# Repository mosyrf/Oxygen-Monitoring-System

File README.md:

# Oxygen-Monitoring-System
This was my second year project as an electrical engineering student, and it was quite difficult because it used an STM32 controller, which I was not familiar with. The project was also considered a failure because it did not produce any final product, only electrical designs and simulations.

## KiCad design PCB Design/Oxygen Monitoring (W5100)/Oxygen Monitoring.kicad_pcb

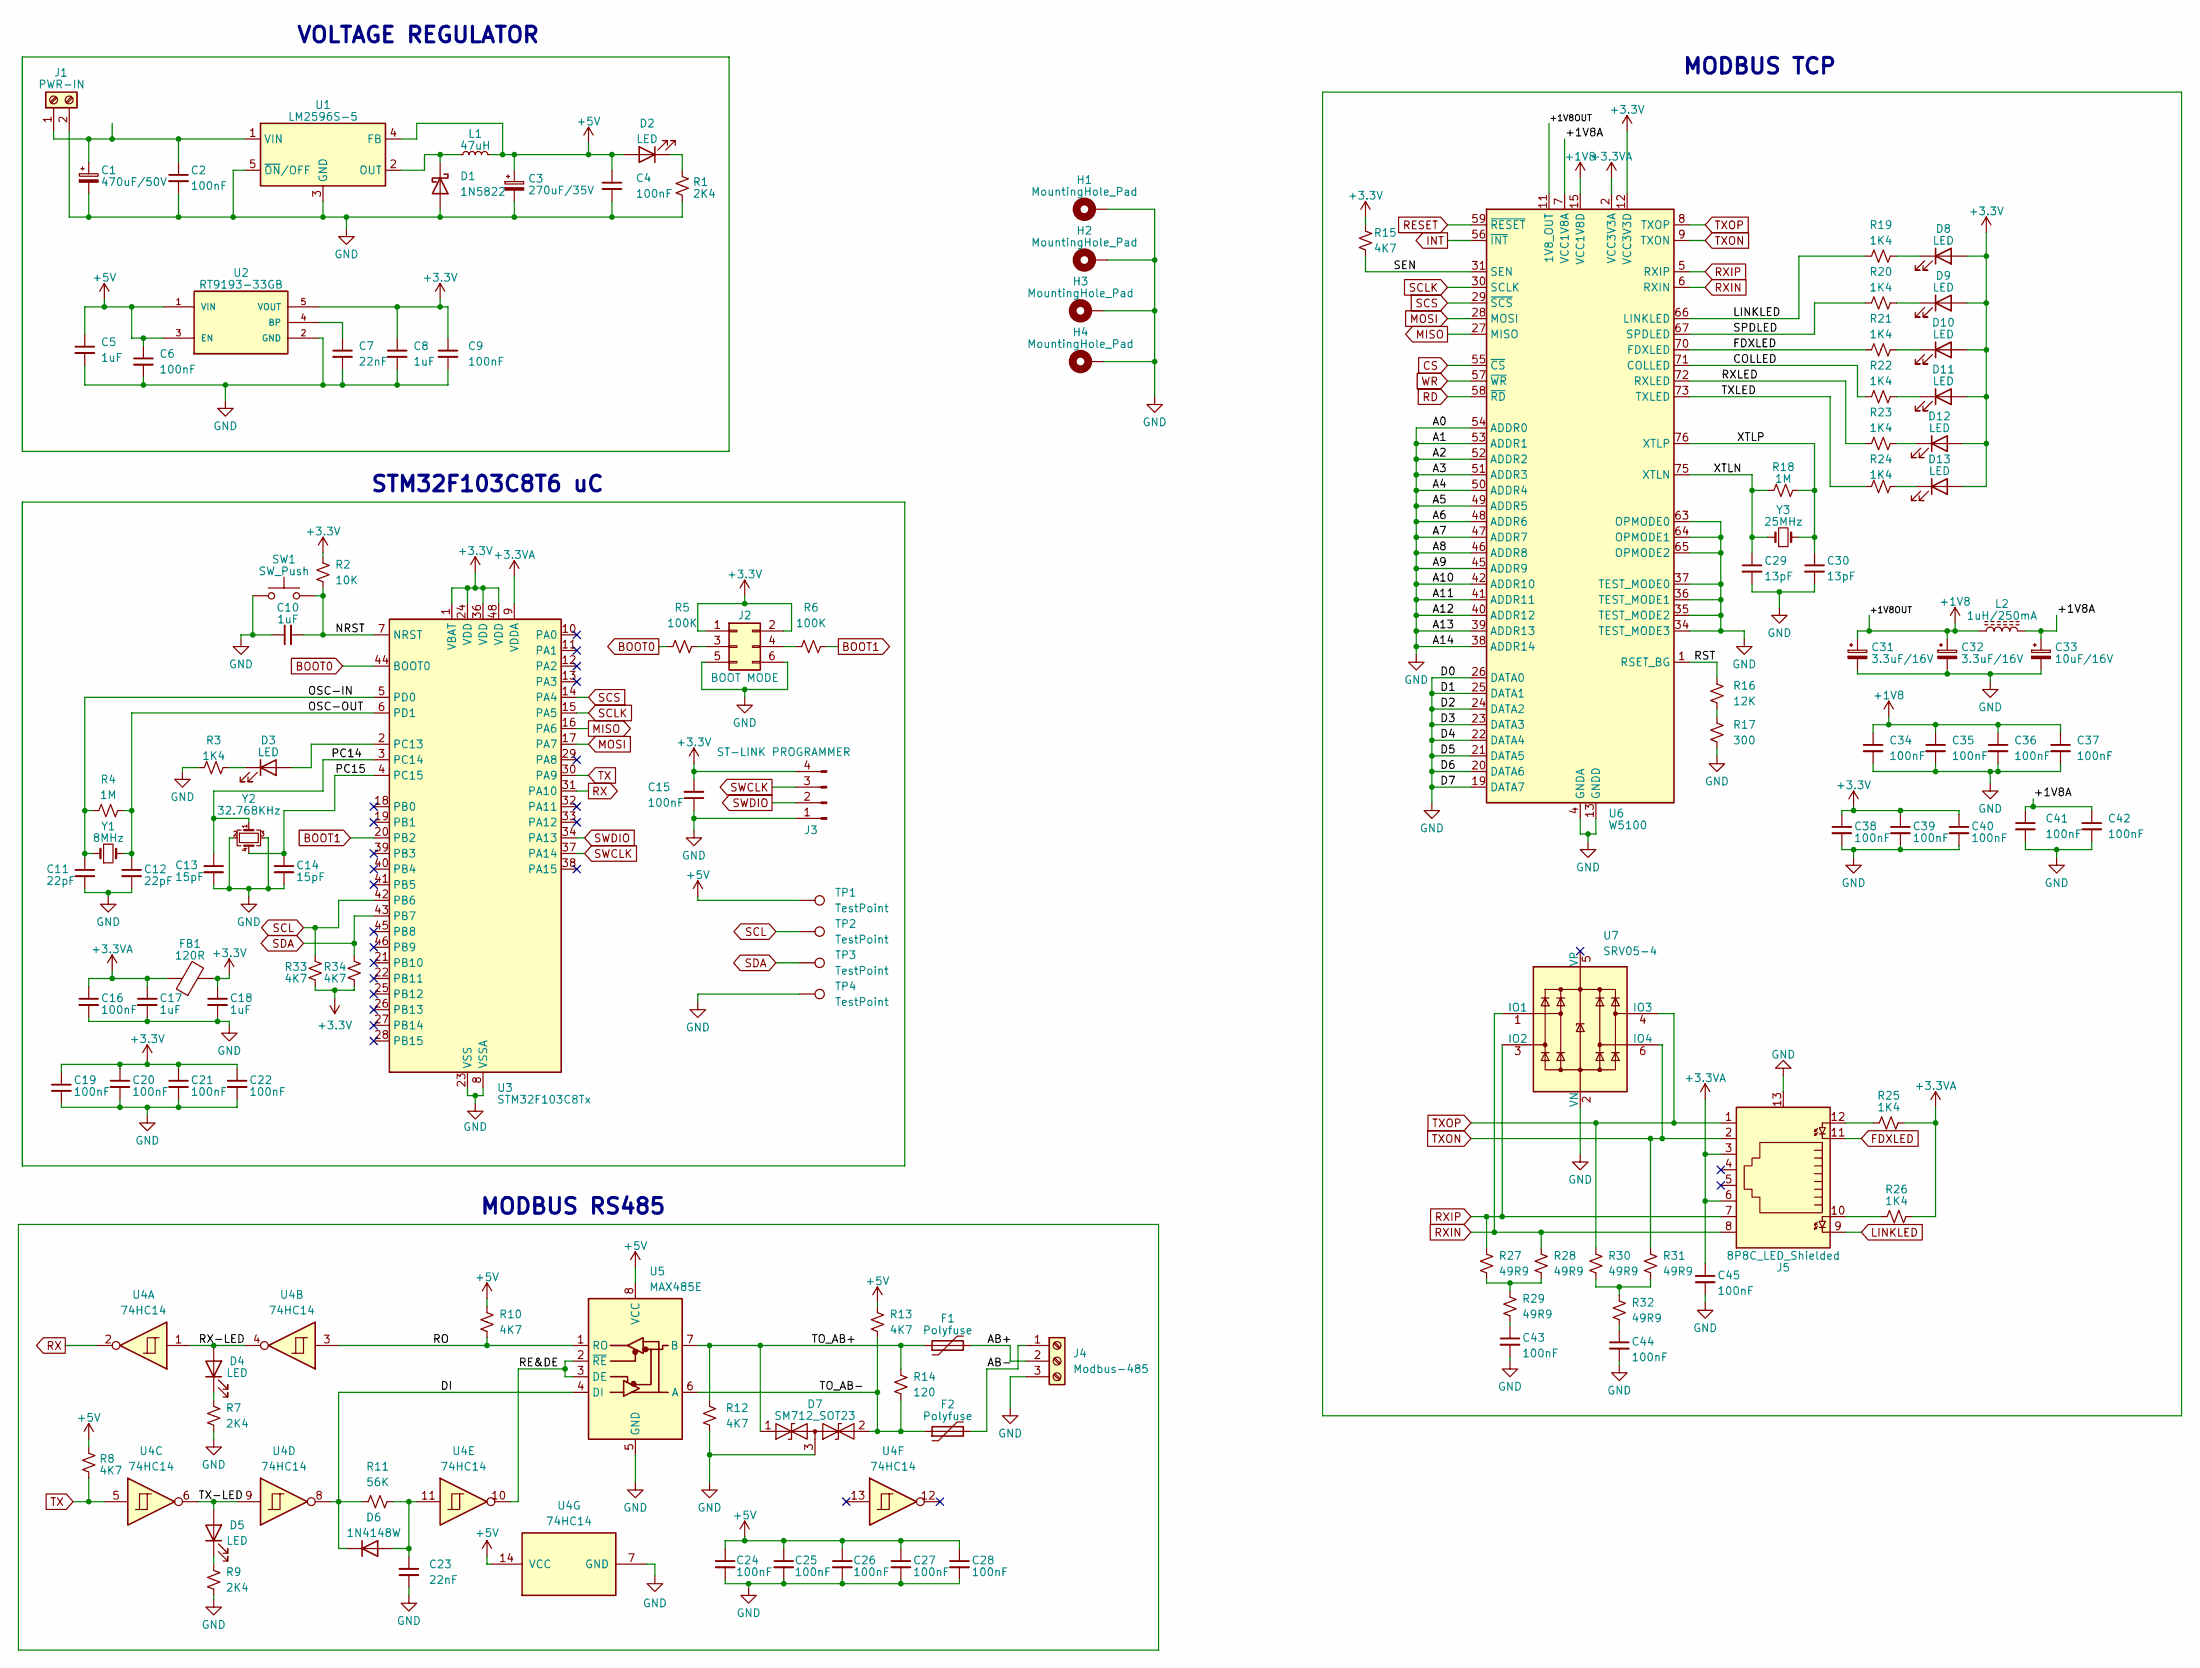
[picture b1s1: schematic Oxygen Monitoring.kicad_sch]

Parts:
C1: 470uF/50V; CP_Radial_D10.0mm_P7.50mm
C2, C4, C6, C9, C15, C16, C19, C20, C21, C22, C24, C25, C26, C27, C28, C34, C35, C36, C37, C38, C39, C40, C41, C42, C43, C44, C45: 100nF; C_0805_2012Metric
C3: 270uF/35V; CP_Radial_D8.0mm_P5.00mm
C5, C8, C10, C17, C18: 1uF; C_0805_2012Metric
C7, C23: 22nF; C_0805_2012Metric
C11, C12: 22pF; C_0805_2012Metric
C13, C14: 15pF; C_0805_2012Metric
C29, C30: 13pF; C_0805_2012Metric
C31, C32: 3.3uF/16V; CP_Radial_D4.0mm_P2.00mm
C33: 10uF/16V; CP_Radial_D5.0mm_P2.00mm
D1: 1N5822; D_DO-201AD_P12.70mm_Horizontal
D2, D3, D4, D5, D8, D9, D10, D11, D12, D13: LED; LED_0805_2012Metric
D6: 1N4148W; D_SOD-123
D7: SM712_SOT23; SOT-23
F1, F2: Polyfuse; Fuse_Littelfuse_395Series
FB1: 120R; L_0805_2012Metric
H1, H2, H3, H4: MountingHole_Pad; MountingHole_3mm_Pad_Via
J1: PWR-IN; TerminalBlock_Phoenix_PT-1,5-2-5.0-H_1x02_P5.00mm_Horizontal
J2: BOOT MODE; PinHeader_2x03_P2.54mm_Vertical
J3: ST-LINK PROGRAMMER; PinHeader_1x04_P2.54mm_Vertical
J4: Modbus-485; TerminalBlock_Phoenix_PT-1,5-3-5.0-H_1x03_P5.00mm_Horizontal
J5: 8P8C_LED_Shielded; RJ45_Cetus_J1B1211CCD_Horizontal
L1: 47uH; L_12x12mm_H4.5mm
L2: 1uH/250mA; L_0805_2012Metric
R1, R7, R9: 2K4; R_0805_2012Metric
R2: 10K; R_0805_2012Metric
R3, R19, R20, R21, R22, R23, R24, R25, R26: 1K4; R_0805_2012Metric
R4, R18: 1M; R_0805_2012Metric
R5, R6: 100K; R_0805_2012Metric
R8, R10, R12, R13, R15, R33, R34: 4K7; R_0805_2012Metric
R11: 56K; R_0805_2012Metric
R14: 120; R_0805_2012Metric
R16: 12K; R_0805_2012Metric
R17: 300; R_0805_2012Metric
R27, R28, R29, R30, R31, R32: 49R9; R_0805_2012Metric
SW1: SW_Push; SW_SPST_CK_RS282G05A3
TP1, TP2, TP3, TP4: TestPoint; SolderWirePad_1x01_SMD_1x2mm
U1: LM2596S-5; TO-263-5_TabPin3
U2: RT9193-33GB; SOT94P279X129-5N
U3: STM32F103C8Tx; LQFP-48_7x7mm_P0.5mm
U4: 74HC14; DIP-14_W7.62mm_SMDSocket_SmallPads
U5: MAX485E; DIP-8_W7.62mm_SMDSocket_SmallPads
U6: W5100; LQFP-80_10x10mm_P0.4mm
U7: SRV05-4; SOT-23-6
Y1: 8MHz; Crystal_HC49-U_Vertical
Y2: 32.768KHz; Crystal_SMD_SeikoEpson_MC156-4Pin_7.1x2.5mm_HandSoldering
Y3: 25MHz; Crystal_HC49-U_Vertical

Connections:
+1V8: C31.1, C32.1, C34.1, C35.1, C36.1, C37.1, L2.1, U6.11 (1V8_OUT), U6.15 (VCC1V8D), U6.16 (VCC1V8D), U6.33 (VCC1V8D), U6.69 (VCC1V8D)
+3.3V: C8.1, C9.1, C15.2, C18.1, C19.1, C20.1, C21.1, C22.1, C38.1, C39.1, C40.1, D8.2 (A), D9.2 (A), D10.2 (A), D11.2 (A), D12.2 (A), D13.2 (A), FB1.2, J2.1, J2.2, J3.4, R2.1, R15.2, R33.2, R34.2, U2.5 (VOUT), U3.1 (VBAT), U3.24 (VDD), U3.36 (VDD), U3.48 (VDD), U6.12 (VCC3V3D), U6.18 (VCC3V3D), U6.44 (VCC3V3D)
+3.3VA: C16.1, C17.1, C45.1, FB1.1, J5.3, J5.6, R25.2, R26.2, U3.9 (VDDA), U6.2 (VCC3V3A)
+5V: C3.1, C4.1, C5.1, C6.1, C24.1, C25.1, C26.1, C27.1, C28.1, D2.2 (A), L1.2, R8.2, R10.2, R13.2, TP1.1, U1.4 (FB), U2.1 (VIN), U2.3 (EN), U4.14 (VCC), U5.8 (VCC)
/+1V8A: C33.1, C41.1, C42.1, L2.2, U6.7 (VCC1V8A), U6.74 (VCC1V8A)
/AB+: F1.2, J4.2
/AB-: F2.2, J4.1
/COLLED: R22.1, U6.71 (COLLED)
/DI: D6.1 (K), R11.2, U4.8, U5.4 (DI)
/NRST: C10.2, R2.2, SW1.2, U3.7 (NRST)
/OSC-IN: C11.1, R4.1, U3.5 (PD0), Y1.1
/OSC-OUT: C12.1, R4.2, U3.6 (PD1), Y1.2
/PC14: C13.1, U3.3 (PC14), Y2.1
/PC15: C14.1, U3.4 (PC15), Y2.4
/RE&DE: U4.10, U5.2 (~RE), U5.3 (DE)
/RO: R10.1, U4.3, U5.1 (RO)
/RST: R16.1, U6.1 (RSET_BG)
/RX-LED: D4.2 (A), U4.1, U4.4
/RXLED: R23.1, U6.72 (RXLED)
/SEN: R15.1, U6.31 (SEN)
/SPDLED: R20.1, U6.67 (SPDLED)
/TO_AB+: D7.1 (A1), F1.1, R12.2, R14.2, U5.7 (B)
/TO_AB-: D7.2 (A2), F2.1, R13.1, R14.1, U5.6 (A)
/TX-LED: D5.2 (A), U4.6, U4.9
/TXLED: R24.1, U6.73 (TXLED)
/XTLN: C29.1, R18.1, U6.75 (XTLN), Y3.1
/XTLP: C30.1, R18.2, U6.76 (XTLP), Y3.2
BOOT0: R5.1, U3.44 (BOOT0)
BOOT1: R6.2, U3.20 (PB2)
CS: U6.55 (~CS)
FDXLED: J5.11, R21.1, U6.70 (FDXLED)
GND: C1.2, C2.2, C3.2, C4.2, C5.2, C6.2, C7.2, C8.2, C9.2, C10.1, C11.2, C12.2, C13.2, C14.2, C15.1, C16.2, C17.2, C18.2, C19.2, C20.2, C21.2, C22.2, C23.2, C24.2, C25.2, C26.2, C27.2, C28.2, C29.2, C30.2, C31.2, C32.2, C33.2, C34.2, C35.2, C36.2, C37.2, C38.2, C39.2, C40.2, C41.2, C42.2, C43.2, C44.2, C45.2, D1.2 (A), D7.3 (common), H1.1, H2.1, H3.1, H4.1, J1.2, J2.5, J2.6, J3.1, J4.3, J5.13, R1.2, R3.1, R7.1, R9.1, R12.1, R17.1, SW1.1, TP4.1, U1.3 (GND), U1.5 (~ON/OFF), U2.2 (GND), U3.8 (VSSA), U3.23 (VSS), U3.35 (VSS), U3.47 (VSS), U4.7 (GND), U5.5 (GND), U6.4 (GNDA), U6.10 (GNDA), U6.13 (GNDD), U6.14 (GNDD), U6.17 (GNDD), U6.19 (DATA7), U6.20 (DATA6), U6.21 (DATA5), U6.22 (DATA4), U6.23 (DATA3), U6.24 (DATA2), U6.25 (DATA1), U6.26 (DATA0), U6.32 (GNDD), U6.34 (TEST_MODE3), U6.35 (TEST_MODE2), U6.36 (TEST_MODE1), U6.37 (TEST_MODE0), U6.38 (ADDR14), U6.39 (ADDR13), U6.40 (ADDR12), U6.41 (ADDR11), U6.42 (ADDR10), U6.43 (GNDD), U6.45 (ADDR9), U6.46 (ADDR8), U6.47 (ADDR7), U6.48 (ADDR6), U6.49 (ADDR5), U6.50 (ADDR4), U6.51 (ADDR3), U6.52 (ADDR2), U6.53 (ADDR1), U6.54 (ADDR0), U6.63 (OPMODE0), U6.64 (OPMODE1), U6.65 (OPMODE2), U6.68 (GNDD), U6.77 (GNDA), U7.2 (VN), Y2.2, Y2.3
INT: U6.56 (~INT)
LINKLED: J5.9, R19.1, U6.66 (LINKLED)
MISO: U3.16 (PA6), U6.27 (MISO)
MOSI: U3.17 (PA7), U6.28 (MOSI)
unnamed: C43.1, R29.2
unnamed: C44.1, R32.2
unnamed: D1.1 (K), L1.1, U1.2 (OUT)
unnamed: D2.1 (K), R1.1
unnamed: D3.2 (A), U3.2 (PC13)
unnamed: D3.1 (K), R3.2
unnamed: D4.1 (K), R7.2
unnamed: D5.1 (K), R9.2
unnamed: C23.1, D6.2 (A), R11.1, U4.11
unnamed: D8.1 (K), R19.2
unnamed: D9.1 (K), R20.2
unnamed: D10.1 (K), R21.2
unnamed: D11.1 (K), R22.2
unnamed: D12.1 (K), R23.2
unnamed: D13.1 (K), R24.2
unnamed: C1.1, C2.1, J1.1, U1.1 (VIN)
unnamed: J2.3, R5.2
unnamed: J2.4, R6.1
unnamed: J5.10, R26.1
unnamed: J5.12, R25.1
unnamed: R16.2, R17.2
unnamed: R27.2, R28.2, R29.1
unnamed: R30.2, R31.2, R32.1
unnamed: C7.1, U2.4 (BP)
RD: U6.58 (~RD)
RESET: U6.59 (~RESET)
RX: U3.31 (PA10), U4.2
RXIN: J5.8, R28.1, U6.6 (RXIN), U7.1 (IO1)
RXIP: J5.7, R27.1, U6.5 (RXIP), U7.3 (IO2)
SCL: R33.1, TP2.1, U3.42 (PB6)
SCLK: U3.15 (PA5), U6.30 (SCLK)
SCS: U3.14 (PA4), U6.29 (~SCS)
SDA: R34.1, TP3.1, U3.43 (PB7)
SWCLK: J3.3, U3.37 (PA14)
SWDIO: J3.2, U3.34 (PA13)
TX: R8.1, U3.30 (PA9), U4.5
TXON: J5.2, R31.1, U6.9 (TXON), U7.6 (IO4)
TXOP: J5.1, R30.1, U6.8 (TXOP), U7.4 (IO3)
WR: U6.57 (~WR)

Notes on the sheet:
VOLTAGE REGULATOR
MODBUS TCP
STM32F103C8T6 uC
MODBUS RS485

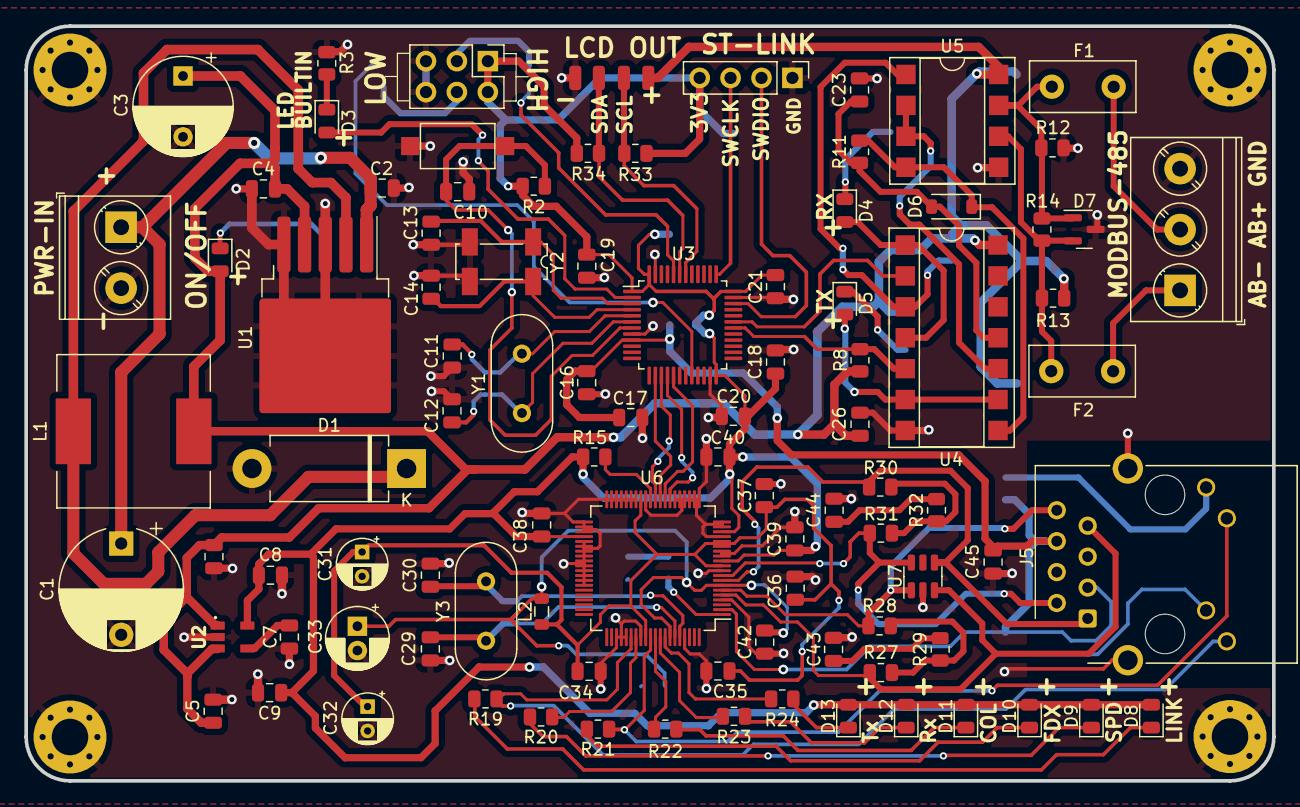
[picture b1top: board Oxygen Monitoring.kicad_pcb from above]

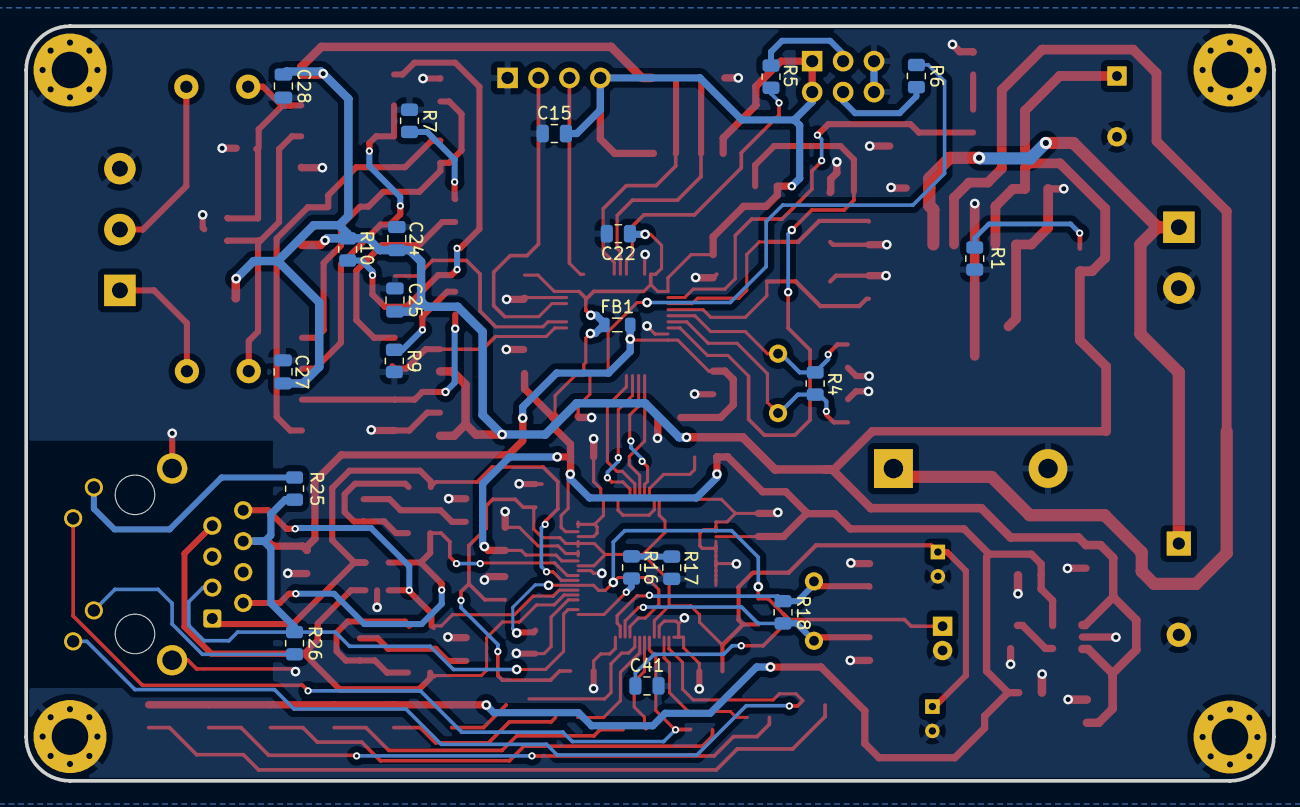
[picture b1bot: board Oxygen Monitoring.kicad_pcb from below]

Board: 2 copper layers, 102.5 x 62.0 mm, 121 parts (20 on the bottom side), 70 nets.

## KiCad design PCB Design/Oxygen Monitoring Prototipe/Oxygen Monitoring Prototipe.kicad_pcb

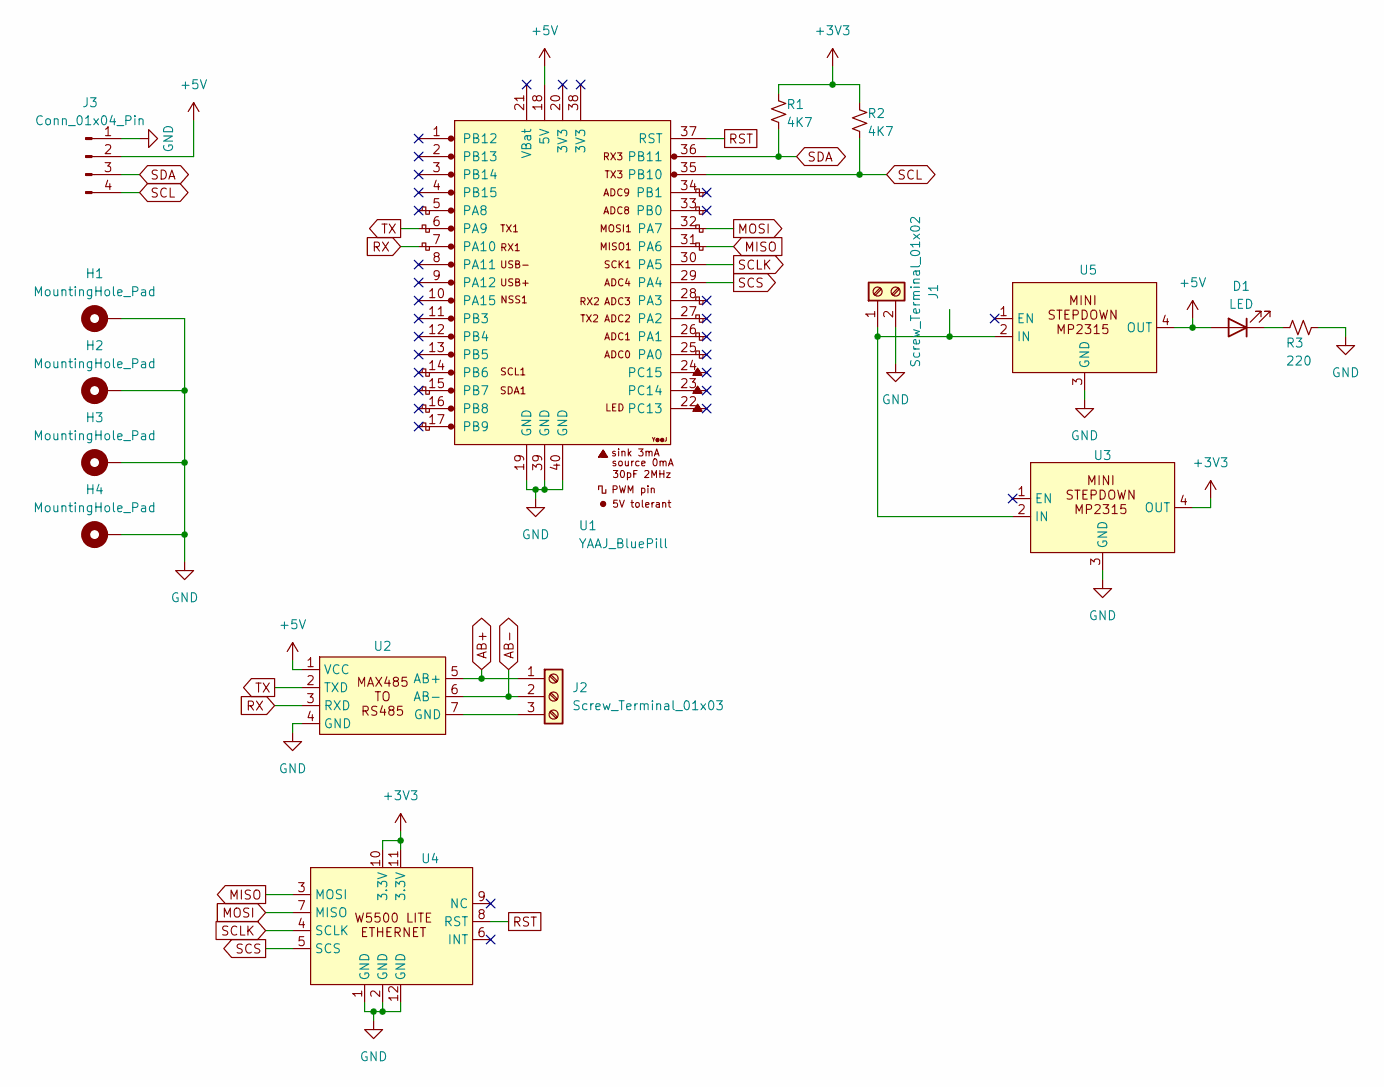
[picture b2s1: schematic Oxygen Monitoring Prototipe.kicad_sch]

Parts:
D1: LED; LED_D5.0mm
H1, H2, H3, H4: MountingHole_Pad; MountingHole_3.2mm_M3_Pad_Via
J1: Screw_Terminal_01x02; TerminalBlock_Phoenix_MKDS-3-2-5.08_1x02_P5.08mm_Horizontal
J2: Screw_Terminal_01x03; TerminalBlock_Phoenix_MKDS-3-3-5.08_1x03_P5.08mm_Horizontal
J3: Conn_01x04_Pin; PinHeader_1x04_P2.54mm_Vertical
R1, R2: 4K7; R_Axial_DIN0204_L3.6mm_D1.6mm_P5.08mm_Horizontal
R3: 220; R_Axial_DIN0204_L3.6mm_D1.6mm_P5.08mm_Horizontal
U1: YAAJ_BluePill; YAAJ_BluePill_1
U2: MAX485_AutoSwitching&Protection
U3, U5: MP2315_Module
U4: W5500_Lite

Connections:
+3V3: R1.1, R2.1, U3.4 (OUT), U4.10 (3.3V), U4.11 (3.3V)
+5V: D1.2 (A), J3.2, U1.18 (5V), U2.1 (VCC), U5.4 (OUT)
AB+: J2.1, U2.5 (AB+)
AB-: J2.2, U2.6 (AB-)
GND: H1.1, H2.1, H3.1, H4.1, J1.2, J3.1, R3.1, U1.19 (GND), U1.39 (GND), U1.40 (GND), U2.4 (GND), U3.3 (GND), U4.1 (GND), U4.2 (GND), U4.12 (GND), U5.3 (GND)
MISO: U1.31 (PA6), U4.3 (MOSI)
MOSI: U1.32 (PA7), U4.7 (MISO)
unnamed: D1.1 (K), R3.2
unnamed: J1.1, U3.2 (IN), U5.2 (IN)
unnamed: J2.3, U2.7 (GND)
RST: U1.37 (RST), U4.8 (RST)
RX: U1.7 (PA10), U2.3 (RXD)
SCL: J3.4, R2.2, U1.35 (PB10)
SCLK: U1.30 (PA5), U4.4 (SCLK)
SCS: U1.29 (PA4), U4.5 (SCS)
SDA: J3.3, R1.2, U1.36 (PB11)
TX: U1.6 (PA9), U2.2 (TXD)

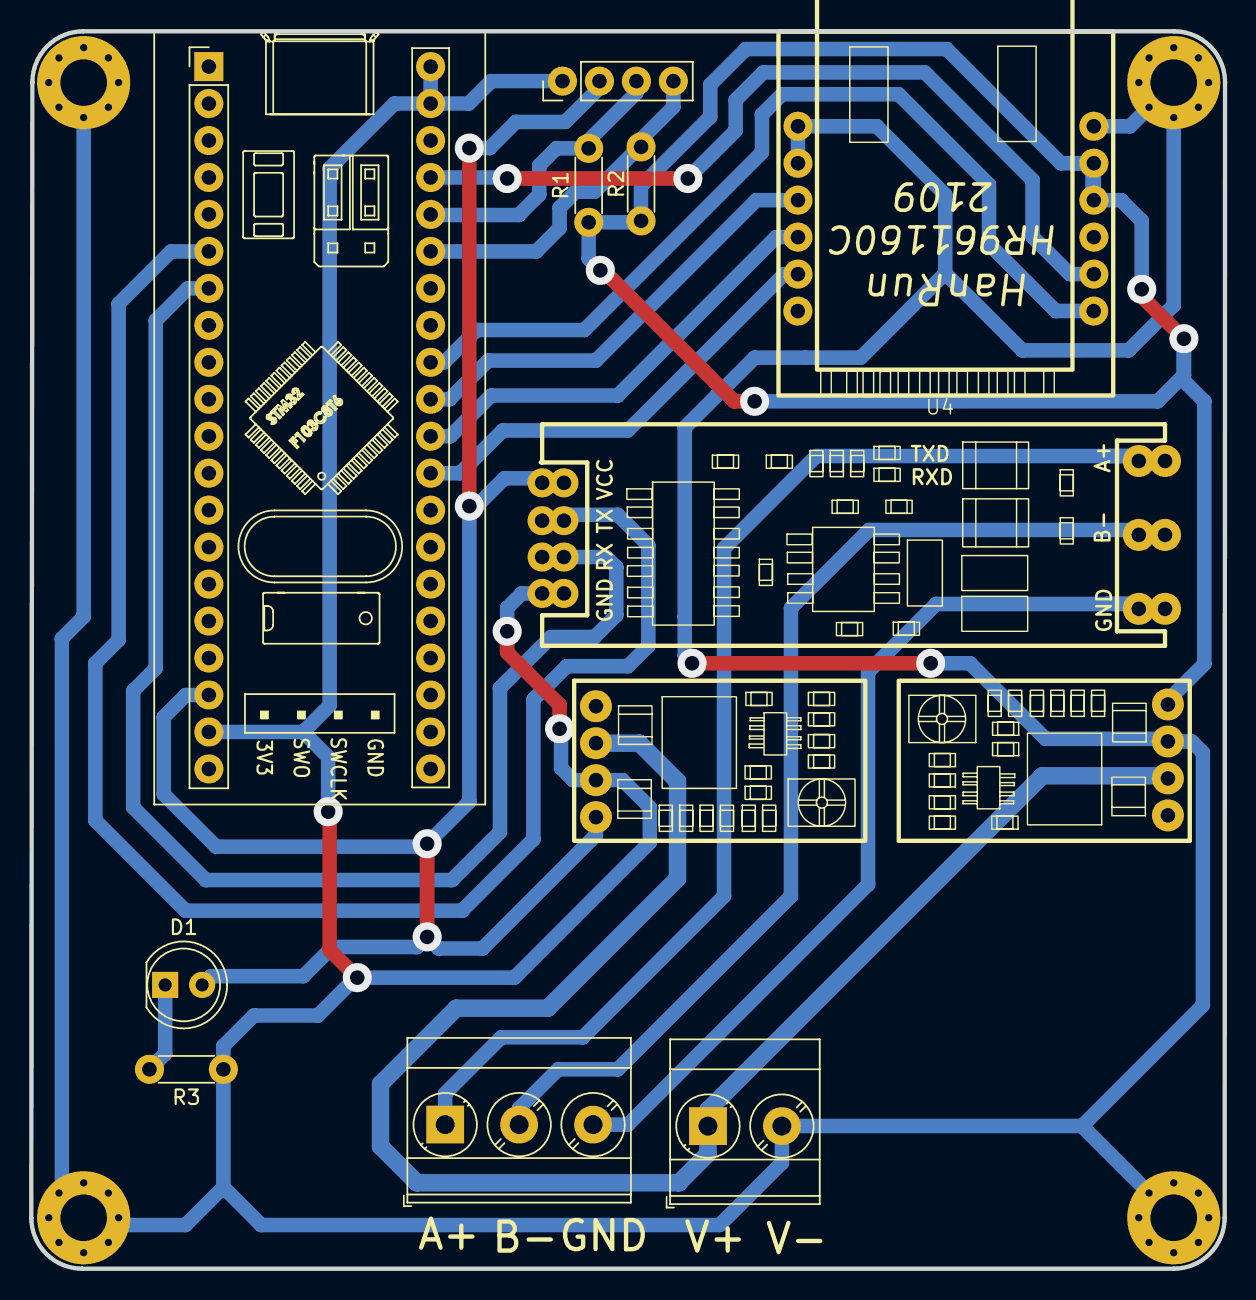
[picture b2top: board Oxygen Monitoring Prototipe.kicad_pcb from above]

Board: 2 copper layers, 82.0 x 85.0 mm, 16 parts (0 on the bottom side), 17 nets.

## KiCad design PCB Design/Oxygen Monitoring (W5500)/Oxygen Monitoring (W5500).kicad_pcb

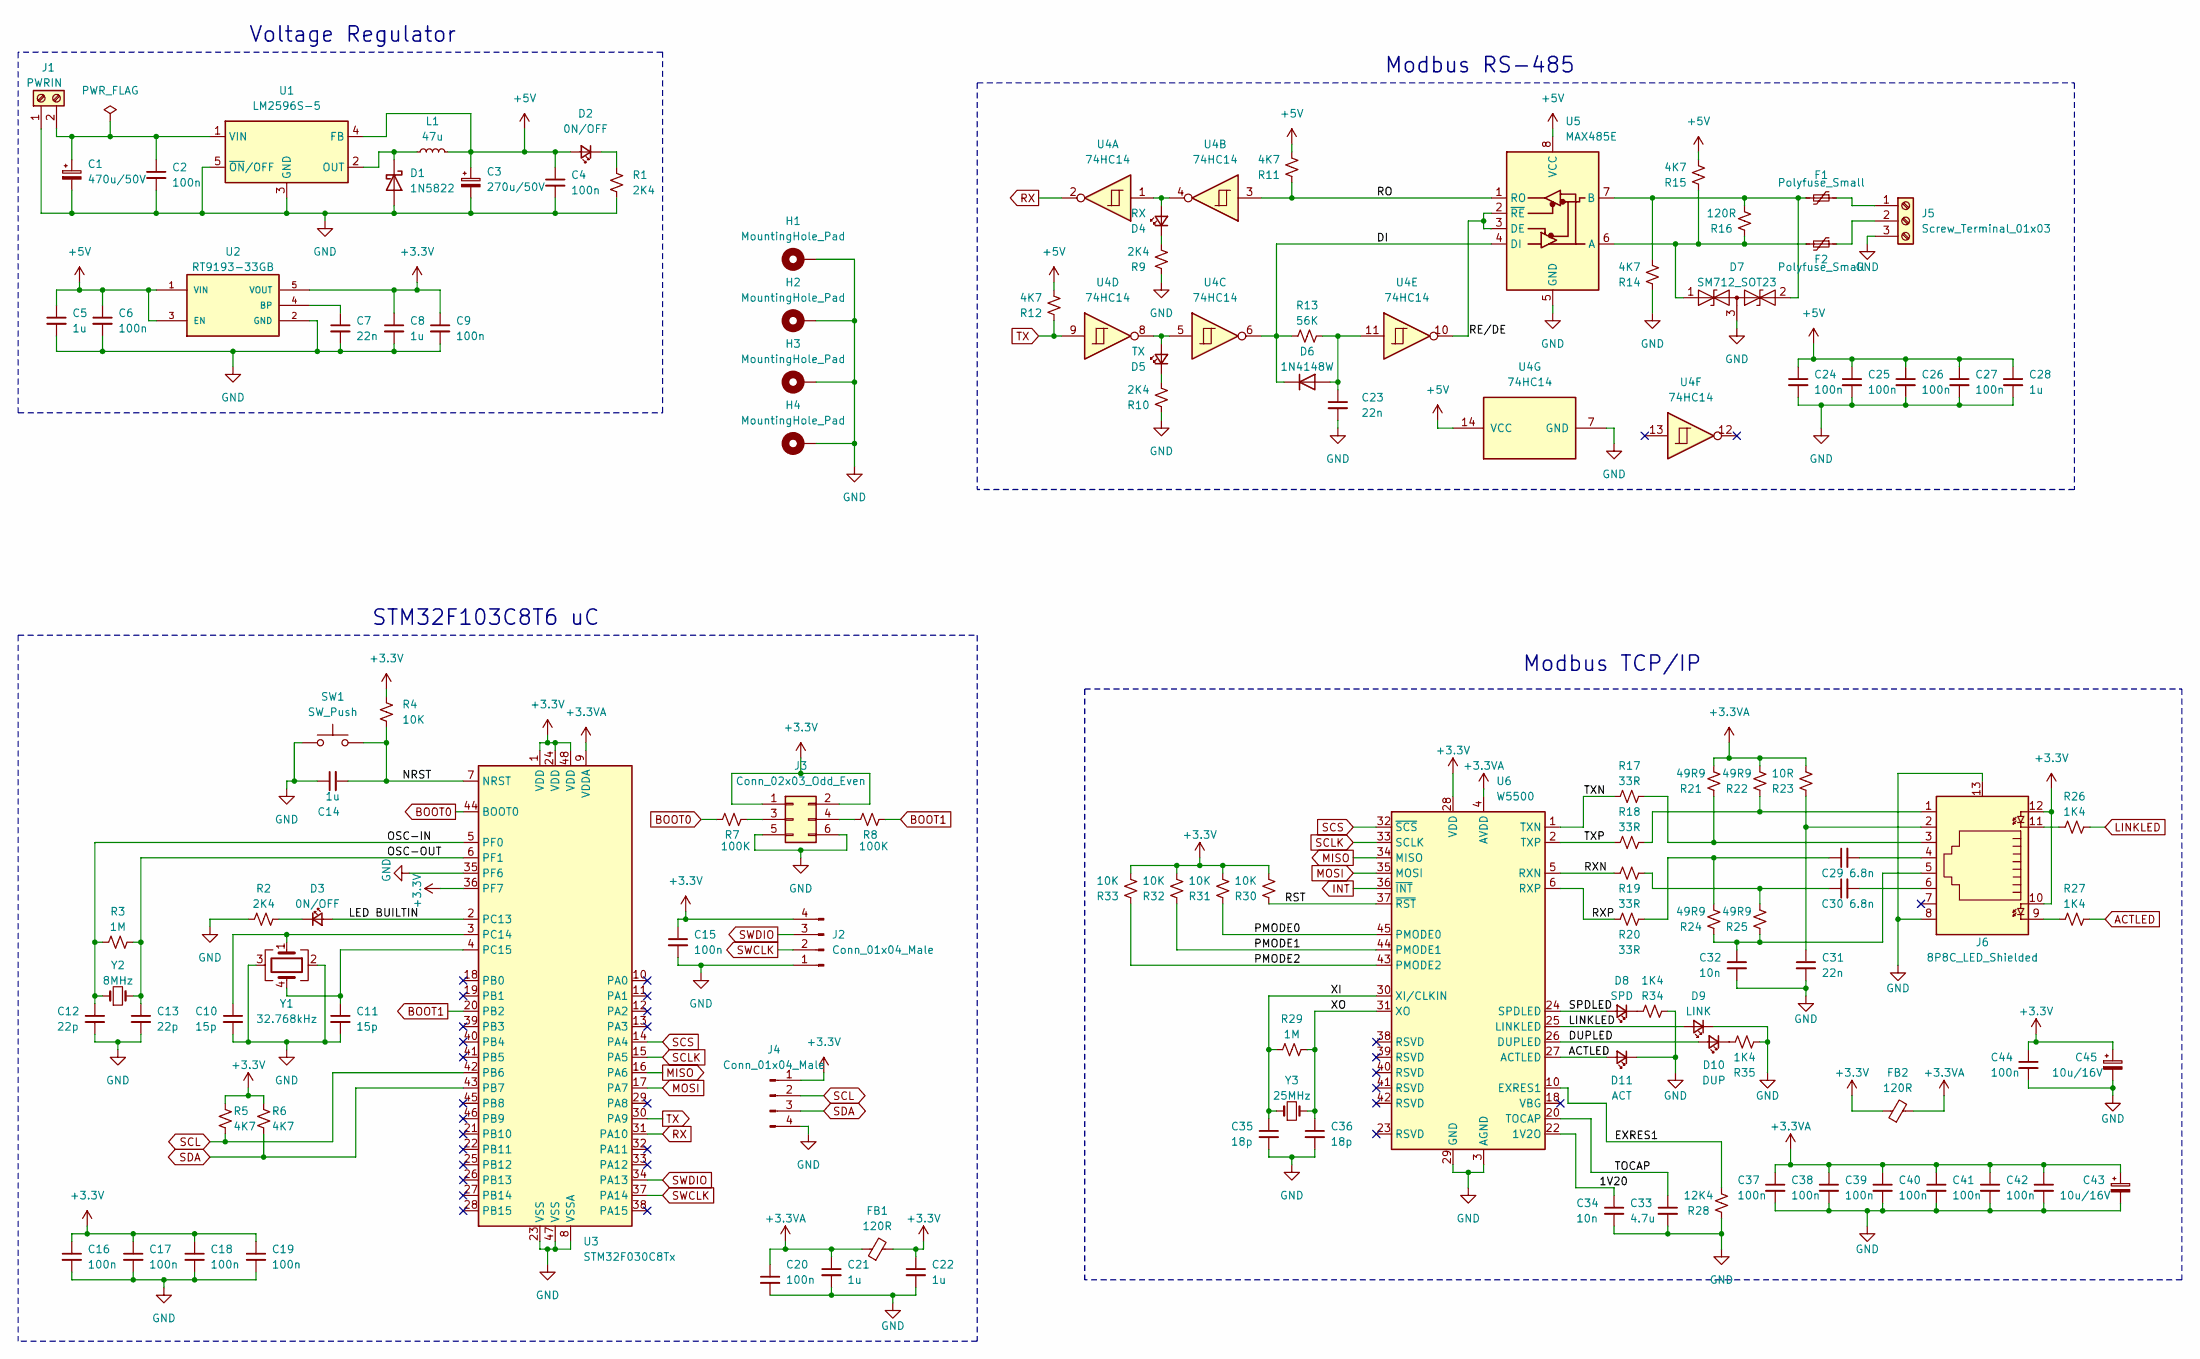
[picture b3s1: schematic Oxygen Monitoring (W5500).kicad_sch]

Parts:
C1: 470u/50V; CP_Radial_D6.3mm_P2.50mm
C2, C4, C6, C9, C15, C16, C17, C18, C19, C20, C24, C25, C26, C27, C37, C38, C39, C40, C41, C42, C44: 100n; C_0805_2012Metric_Pad1.18x1.45mm_HandSolder
C3: 270u/50V; CP_Radial_D5.0mm_P2.50mm
C5, C8, C14, C21, C22, C28: 1u; C_0805_2012Metric_Pad1.18x1.45mm_HandSolder
C7, C23, C31: 22n; C_0805_2012Metric_Pad1.18x1.45mm_HandSolder
C10, C11: 15p; C_0805_2012Metric_Pad1.18x1.45mm_HandSolder
C12, C13: 22p; C_0805_2012Metric_Pad1.18x1.45mm_HandSolder
C29, C30: 6.8n; C_0805_2012Metric_Pad1.18x1.45mm_HandSolder
C32, C34: 10n; C_0805_2012Metric_Pad1.18x1.45mm_HandSolder
C33: 4.7u; C_0805_2012Metric_Pad1.18x1.45mm_HandSolder
C35, C36: 18p; C_0805_2012Metric_Pad1.18x1.45mm_HandSolder
C43, C45: 10u/16V; CP_Radial_D4.0mm_P1.50mm
D1: 1N5822; D_DO-201AD_P15.24mm_Horizontal
D2, D3: 0N/OFF; LED_0805_2012Metric_Pad1.15x1.40mm_HandSolder
D4: RX; LED_0805_2012Metric_Pad1.15x1.40mm_HandSolder
D5: TX; LED_0805_2012Metric_Pad1.15x1.40mm_HandSolder
D6: 1N4148W; D_SOD-123
D7: SM712_SOT23; SOT-23
D8: SPD; LED_0805_2012Metric_Pad1.15x1.40mm_HandSolder
D9: LINK; LED_0805_2012Metric_Pad1.15x1.40mm_HandSolder
D10: DUP; LED_0805_2012Metric_Pad1.15x1.40mm_HandSolder
D11: ACT; LED_0805_2012Metric_Pad1.15x1.40mm_HandSolder
F1, F2: Polyfuse_Small; Fuse_1210_3225Metric_Pad1.42x2.65mm_HandSolder
FB1, FB2: 120R; L_0805_2012Metric_Pad1.15x1.40mm_HandSolder
H1, H2, H3, H4: MountingHole_Pad; MountingHole_3.2mm_M3_Pad_Via
J1: PWRIN; TerminalBlock_Phoenix_MKDS-1,5-2-5.08_1x02_P5.08mm_Horizont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
J2: Conn_01x04_Male; PinHeader_1x04_P2.54mm_Vertical
J3: Conn_02x03_Odd_Even; PinHeader_2x03_P2.54mm_Vertical
J4: Conn_01x04_Male; Molex_KK-254_AE-6410-04A_1x04_P2.54mm_Vertical
J5: Screw_Terminal_01x03; TerminalBlock_Phoenix_MKDS-1,5-3-5.08_1x03_P5.08mm_Horizont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
J6: 8P8C_LED_Shielded; RJ45_Cetus_J1B1211CCD_Horizontal
L1: 47u; L_12x12mm_H6mm
R1, R2, R9, R10: 2K4; R_0805_2012Metric_Pad1.20x1.40mm_HandSolder
R3, R29: 1M; R_0805_2012Metric_Pad1.20x1.40mm_HandSolder
R4, R30, R31, R32, R33: 10K; R_0805_2012Metric_Pad1.20x1.40mm_HandSolder
R5, R6, R11, R12, R14, R15: 4K7; R_0805_2012Metric_Pad1.20x1.40mm_HandSolder
R7, R8: 100K; R_0805_2012Metric_Pad1.20x1.40mm_HandSolder
R13: 56K; R_0805_2012Metric_Pad1.20x1.40mm_HandSolder
R16: 120R; R_0805_2012Metric_Pad1.20x1.40mm_HandSolder
R17, R18, R19, R20: 33R; R_0805_2012Metric_Pad1.20x1.40mm_HandSolder
R21, R22, R24, R25: 49R9; R_0805_2012Metric_Pad1.20x1.40mm_HandSolder
R23: 10R; R_0805_2012Metric_Pad1.20x1.40mm_HandSolder
R26, R27, R34, R35: 1K4; R_0805_2012Metric_Pad1.20x1.40mm_HandSolder
R28: 12K4; R_0805_2012Metric_Pad1.20x1.40mm_HandSolder
SW1: SW_Push; SW_SPST_TL3342
U1: LM2596S-5; TO-263-5_TabPin3
U2: RT9193-33GB; SOT-23-5_HandSoldering
U3: STM32F030C8Tx; LQFP-48_7x7mm_P0.5mm
U4: 74HC14; DIP-14_W7.62mm_SMDSocket_SmallPads
U5: MAX485E; DIP-8_W7.62mm_SMDSocket_SmallPads
U6: W5500; LQFP-48_7x7mm_P0.5mm
Y1: 32.768kHz; Crystal_SMD_SeikoEpson_MC156-4Pin_7.1x2.5mm_HandSoldering
Y2: 8MHz; Crystal_HC49-4H_Vertical
Y3: 25MHz; Crystal_HC49-4H_Vertical

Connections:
+3.3V: C8.1, C9.1, C15.1, C16.1, C17.1, C18.1, C19.1, C22.1, C44.1, C45.1, FB1.2, FB2.1, J2.4, J3.1, J3.2, J4.1, J6.10, J6.12, R4.1, R5.1, R6.1, R30.2, R31.2, R32.2, R33.2, U2.5 (VOUT), U3.1 (VDD), U3.24 (VDD), U3.36 (PF7), U3.48 (VDD), U6.28 (VDD)
+3.3VA: C20.1, C21.1, C37.1, C38.1, C39.1, C40.1, C41.1, C42.1, C43.1, FB1.1, FB2.2, R21.2, R22.2, R23.2, U3.9 (VDDA), U6.4 (AVDD), U6.8 (AVDD), U6.11 (AVDD), U6.15 (AVDD), U6.17 (AVDD), U6.21 (AVDD)
+5V: C3.1, C4.1, C5.1, C6.1, C24.1, C25.1, C26.1, C27.1, C28.1, D2.2 (A), L1.2, R11.2, R12.2, R15.2, U1.4 (FB), U2.1 (VIN), U2.3 (EN), U4.14 (VCC), U5.8 (VCC)
/1V20: C34.1, U6.22 (1V2O)
/DI: D6.1 (K), R13.1, U4.6, U5.4 (DI)
/DUPLED: D10.2 (A), U6.26 (DUPLED)
/EXRES1: R28.2, U6.10 (EXRES1)
/LED BUILTIN: D3.2 (A), U3.2 (PC13)
/NRST: C14.2, R4.2, SW1.2, U3.7 (NRST)
/OSC-IN: C12.1, R3.1, U3.5 (PF0), Y2.1
/OSC-OUT: C13.1, R3.2, U3.6 (PF1), Y2.2
/PMODE0: R31.1, U6.45 (PMODE0)
/PMODE1: R32.1, U6.44 (PMODE1)
/PMODE2: R33.1, U6.43 (PMODE2)
/RE/DE: U4.10, U5.2 (~RE), U5.3 (DE)
/RO: R11.1, U4.3, U5.1 (RO)
/RST: R30.1, U6.37 (~RST)
/RXN: R19.1, U6.5 (RXN)
/RXP: R20.1, U6.6 (RXP)
/SPDLED: D8.2 (A), U6.24 (SPDLED)
/TOCAP: C33.1, U6.20 (TOCAP)
/TXN: R17.1, U6.1 (TXN)
/TXP: R18.1, U6.2 (TXP)
/XI: C35.1, R29.1, U6.30 (XI/CLKIN), Y3.1
/XO: C36.1, R29.2, U6.31 (XO), Y3.2
ACTLED: D11.2 (A), R27.2, U6.27 (ACTLED)
BOOT0: R7.2, U3.44 (BOOT0)
BOOT1: R8.1, U3.20 (PB2)
GND: C1.2, C2.2, C3.2, C4.2, C5.2, C6.2, C7.2, C8.2, C9.2, C10.2, C11.2, C12.2, C13.2, C14.1, C15.2, C16.2, C17.2, C18.2, C19.2, C20.2, C21.2, C22.2, C23.2, C24.2, C25.2, C26.2, C27.2, C28.2, C31.2, C32.2, C33.2, C34.2, C35.2, C36.2, C37.2, C38.2, C39.2, C40.2, C41.2, C42.2, C43.2, C44.2, C45.2, D1.2 (A), D7.3 (common), D9.1 (K), D11.1 (K), H1.1, H2.1, H3.1, H4.1, J1.1, J2.1, J3.5, J3.6, J4.4, J5.3, J6.8, J6.13, R1.2, R2.1, R9.1, R10.1, R14.1, R28.1, R34.1, R35.1, SW1.1, U1.3 (GND), U1.5 (~ON/OFF), U2.2 (GND), U3.8 (VSSA), U3.23 (VSS), U3.35 (PF6), U3.47 (VSS), U4.7 (GND), U5.5 (GND), U6.3 (AGND), U6.9 (AGND), U6.14 (AGND), U6.16 (AGND), U6.19 (AGND), U6.29 (GND), U6.48 (AGND), Y1.2, Y1.3
INT: U6.36 (~INT)
LINKLED: D9.2 (A), R26.2, U6.25 (LINKLED)
MISO: U3.16 (PA6), U6.34 (MISO)
MOSI: U3.17 (PA7), U6.35 (MOSI)
unnamed: C1.1, C2.1, J1.2, U1.1 (VIN)
unnamed: C7.1, U2.4 (BP)
unnamed: C10.1, U3.3 (PC14), Y1.1
unnamed: C11.1, U3.4 (PC15), Y1.4
unnamed: C23.1, D6.2 (A), R13.2, U4.11
unnamed: C29.1, R20.2, R24.2
unnamed: C29.2, J6.4
unnamed: C30.1, R19.2, R25.2
unnamed: C30.2, J6.6
unnamed: C31.1, J6.2, R23.1
unnamed: C32.1, J6.5, R24.1, R25.1
unnamed: D1.1 (K), L1.1, U1.2 (OUT)
unnamed: D2.1 (K), R1.1
unnamed: D3.1 (K), R2.2
unnamed: D4.1 (K), R9.2
unnamed: D4.2 (A), U4.1, U4.4
unnamed: D5.1 (K), R10.2
unnamed: D5.2 (A), U4.5, U4.8
unnamed: D7.1 (A1), F2.2, R15.1, R16.1, U5.6 (A)
unnamed: D7.2 (A2), F1.2, R14.2, R16.2, U5.7 (B)
unnamed: D8.1 (K), R34.2
unnamed: D10.1 (K), R35.2
unnamed: F1.1, J5.1
unnamed: F2.1, J5.2
unnamed: J3.3, R7.1
unnamed: J3.4, R8.2
unnamed: J6.1, R18.2, R22.1
unnamed: J6.3, R17.2, R21.1
unnamed: J6.9, R27.1
unnamed: J6.11, R26.1
RX: U3.31 (PA10), U4.2
SCL: J4.2, R5.2, U3.42 (PB6)
SCLK: U3.15 (PA5), U6.33 (SCLK)
SCS: U3.14 (PA4), U6.32 (~SCS)
SDA: J4.3, R6.2, U3.43 (PB7)
SWCLK: J2.2, U3.37 (PA14)
SWDIO: J2.3, U3.34 (PA13)
TX: R12.1, U3.30 (PA9), U4.9

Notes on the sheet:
Voltage Regulator
Modbus TCP/IP
Modbus RS-485
STM32F103C8T6 uC

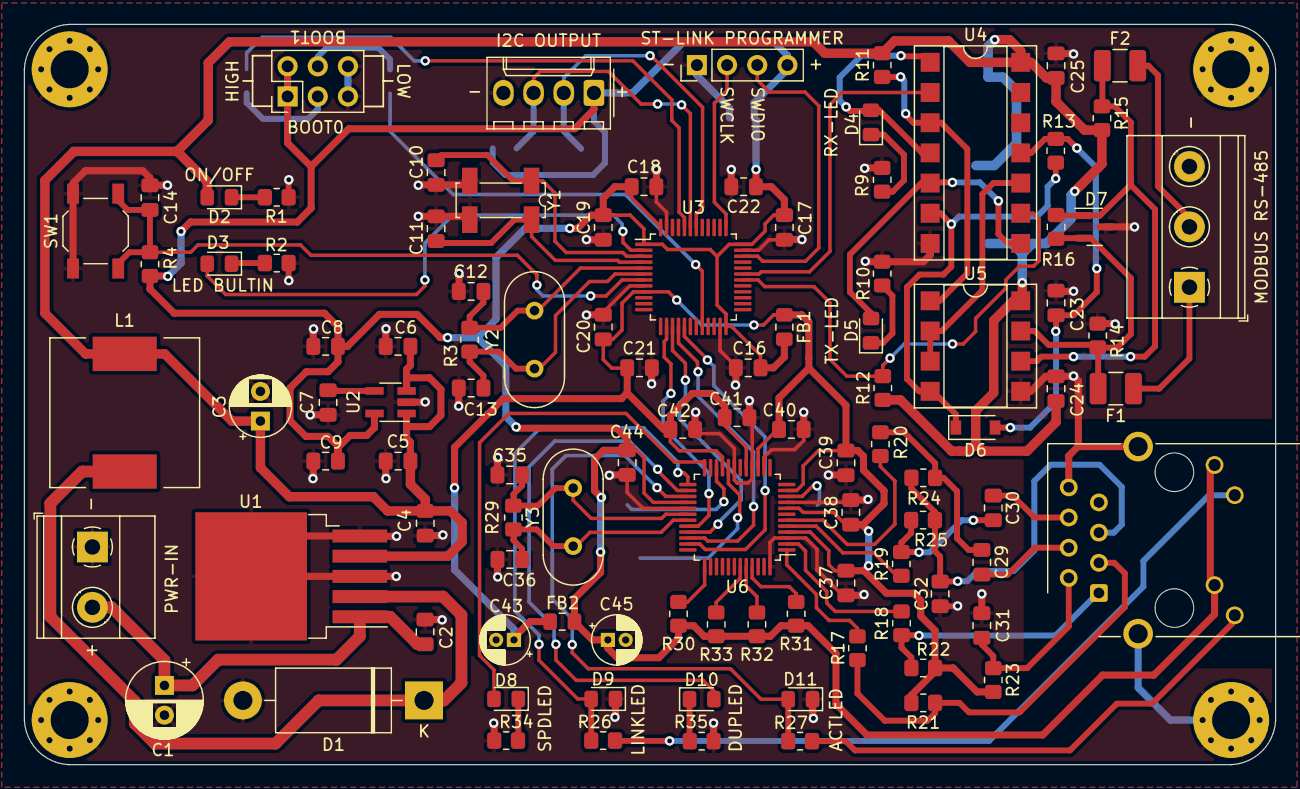
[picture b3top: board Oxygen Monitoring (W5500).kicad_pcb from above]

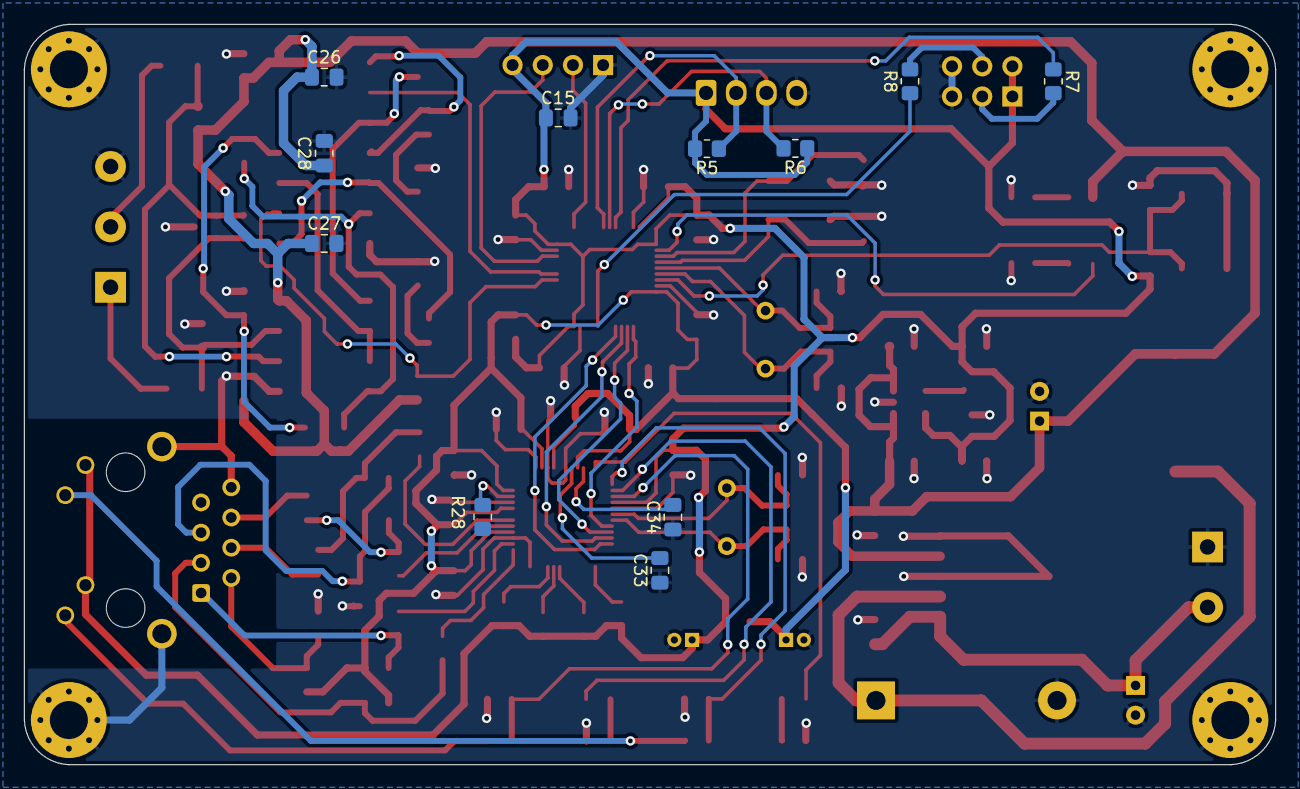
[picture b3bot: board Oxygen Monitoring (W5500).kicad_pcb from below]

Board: 2 copper layers, 105.3 x 62.3 mm, 116 parts (11 on the bottom side), 70 nets.

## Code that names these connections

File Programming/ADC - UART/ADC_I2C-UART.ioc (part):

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Mcu.Name=STM32F103C(8-B)Tx
Mcu.Package=LQFP48
Mcu.UserName=STM32F103C8Tx
PA0-WKUP.Signal=ADCx_IN0
PA10.Mode=Asynchronous
PA10.Signal=USART1_RX
PA13.Mode=Serial_Wire
PA13.Signal=SYS_JTMS-SWDIO
PA14.Mode=Serial_Wire
PA14.Signal=SYS_JTCK-SWCLK
PA9.Mode=Asynchronous
PA9.Signal=USART1_TX
PB6.Mode=I2C
PB6.Signal=I2C1_SCL
PB7.Mode=I2C
PB7.Signal=I2C1_SDA
PD0-OSC_IN.Mode=HSE-External-Oscillator
PD0-OSC_IN.Signal=RCC_OSC_IN
PD1-OSC_OUT.Mode=HSE-External-Oscillator
PD1-OSC_OUT.Signal=RCC_OSC_OUT
RCC.SYSCLKFreq_VALUE=72000000
RCC.SYSCLKSource=RCC_SYSCLKSOURCE_PLLCLK
board=custom

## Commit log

2025-09-01 Create t
2025-09-02 add files
